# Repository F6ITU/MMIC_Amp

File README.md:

# MMIC_Amp
A small RF mmic 20dB preamp for the G6ALU 20 W linear

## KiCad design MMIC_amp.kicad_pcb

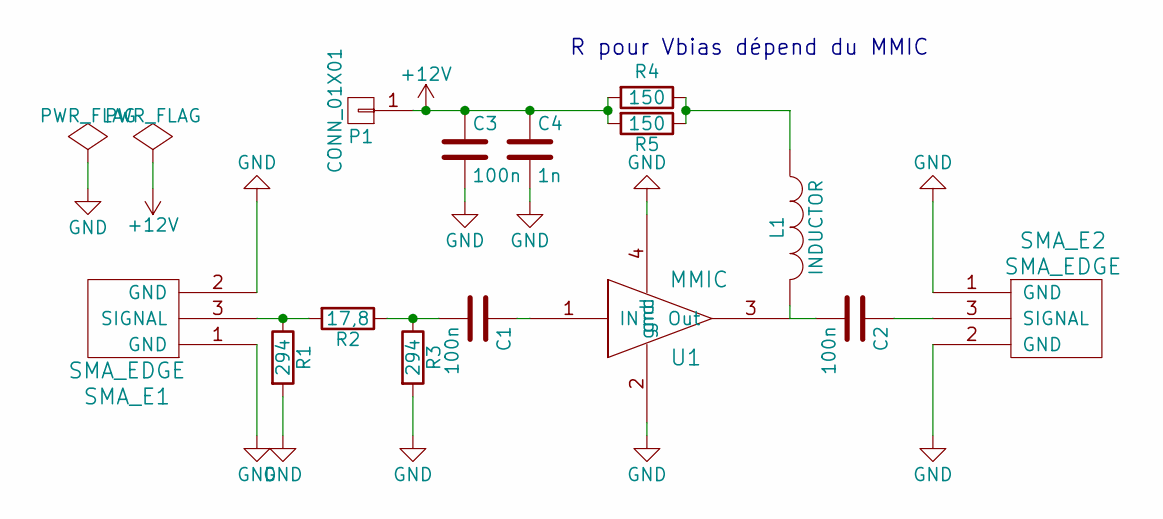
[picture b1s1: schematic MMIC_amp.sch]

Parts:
C1, C2, C3: 100n; C_1206_HandSoldering
C4: 1n; C_1206_HandSoldering
L1: INDUCTOR; C_1210_HandSoldering
P1: CONN_01X01; 1pin
R1, R3: 294; C_0805_HandSoldering
R2: 17,8; C_0805_HandSoldering
R4, R5: 150; C_0805_HandSoldering
SMA_E1, SMA_E2: SMA_EDGE
U1: MMIC

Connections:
+12V: C3.1, C4.1, P1.1, R4.2, R5.2
GND: C3.2, C4.2, R1.2, R3.2, SMA_E1.1 (GND), SMA_E1.2 (GND), SMA_E2.1 (GND), SMA_E2.2 (GND), U1.2 (gnd), U1.4 (gnd)
unnamed: C1.1, U1.1 (IN)
unnamed: C1.2, R2.1, R3.1
unnamed: C2.1, SMA_E2.3 (SIGNAL)
unnamed: C2.2, L1.2, U1.3 (Out)
unnamed: L1.1, R4.1, R5.1
unnamed: R1.1, R2.2, SMA_E1.3 (SIGNAL)

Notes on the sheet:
R pour Vbias dépend du MMIC

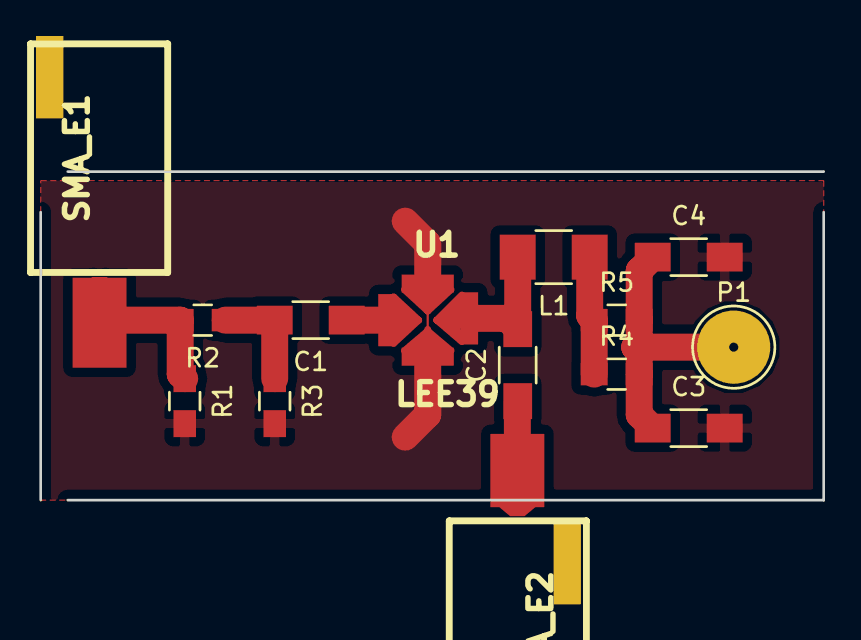
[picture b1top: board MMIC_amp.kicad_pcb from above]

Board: 2 copper layers, 43.5 x 18.2 mm, 14 parts (0 on the bottom side), 8 nets.

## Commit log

2016-05-19 fichier originaux, proto fonctionnel
